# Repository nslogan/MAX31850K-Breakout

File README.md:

# MAX31850K-Breakout

## Description

A small breakout board for the Maxim MAX31850K 1-wire type-K thermocouple amplifier with CJC. Project [available on GitHub](https://github.com/nslogan/MAX31850K-Breakout").

## Production

The board measures 0.85x0.85in (21.62x21.62mm) and is designed for production at [OSH Park](https://www.oshpark.com/). The OSHPark DRU is located in the `res/` folder.

The boards can be purchased [here](https://oshpark.com/shared_projects/TtoEusV0) @ $3.60 for three.

## Parts

All parts on this board are from the [LoganSmith-Eagle-Library](https://github.com/nslogan/LoganSmith-Eagle-Library) available on GitHub (work in progress).

The BOM is located in the `release/` folder, all parts are sourced from Digi-Key.

## Project Structure

This project adheres to this structure:

	[ProjectName]
		README.md
		[release]
			[Major.Minor]
				ProjectName_BOM_Major.Minor.xls or ProjectName_BOM_BOM_Major.Minor.csv
				ProjectName_schematic_Major.Minor.pdf
				ProjectName_board-<top/mid#/bottom>_Major.Minor.png
				ProjectName_Major.Minor.sch
				ProjectName_Major.Minor.brd
				[Gerbers]
					...
			...
		[src]
			[Major.0]
				BoardName.sch
				BoardName.brd
				BOM.xls or BOM.csv
			[Major+1.0]
				...
			...
		[lib]
			...
		[res]
			Manufacturer.dru
			Manufacturer.cam

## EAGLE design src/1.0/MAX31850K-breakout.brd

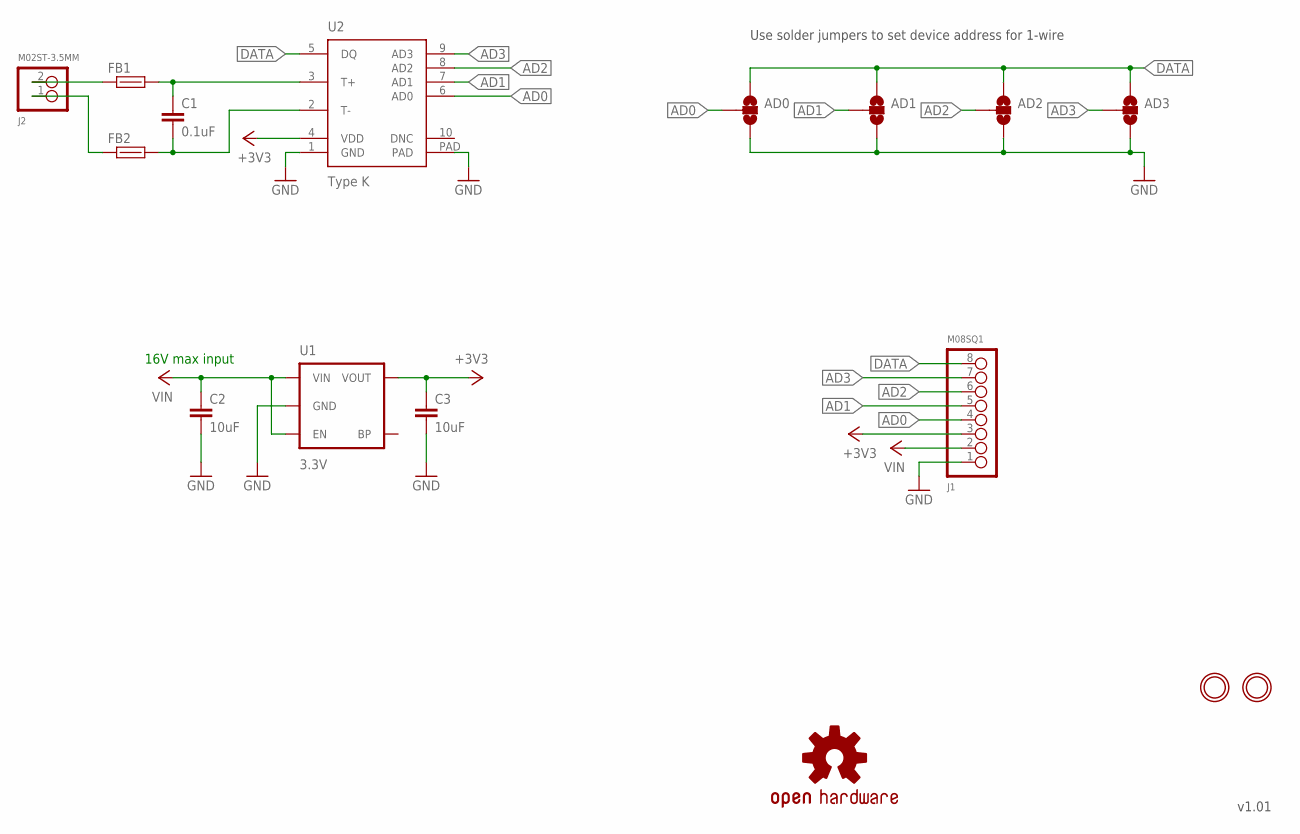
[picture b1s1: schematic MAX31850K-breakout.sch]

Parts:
AD0, AD1, AD2, AD3: SJ_2WAYS; SJ_3
C1: 0.1uF; 0603-CAP
C2: 10uF; 1206-CAP
C3: 10uF; 0805-CAP
FB1, FB2: FB-1K-100MHZ-0603; 0603-RES
J1: M08SQ1; 1X08_SQ1
J2: M02ST-3.5MM; SCREWTERMINAL-3.5MM-2
LOGO1: OSHW-LOGOM; OSHW-LOGO-M
U1: 3.3V; SOT23-5
U2: Type K; 10-TDFN-EP
U$1, U$2: MNTHOLE-2.0; MOUNTINGHOLE_2.0_PLATED

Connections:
+3V3: C3.P$1 (1), J1.3, U1.5 (VOUT), U2.4 (VDD)
AD0: AD0.2, J1.4, U2.6 (AD0)
AD1: AD1.2, J1.5, U2.7 (AD1)
AD2: AD2.2, J1.6, U2.8 (AD2)
AD3: AD3.2, J1.7, U2.9 (AD3)
DATA: AD0.1, AD1.1, AD2.1, AD3.1, J1.8, U2.5 (DQ)
GND: AD0.3, AD1.3, AD2.3, AD3.3, C2.P$4 (2), C3.P$2 (2), J1.1, U1.2 (GND), U2.1 (GND), U2.PAD
TM_FILT: C1.P$2 (2), FB2.P$2 (2), U2.2 (T-)
TM_RAW: FB2.P$1 (1), J2.1
TP_FILT: C1.P$1 (1), FB1.P$2 (2), U2.3 (T+)
TP_RAW: FB1.P$1 (1), J2.2
VIN: C2.P$3 (1), J1.2, U1.1 (VIN), U1.3 (EN)

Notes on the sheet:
16V max input
Use solder jumpers to set device address for 1-wire

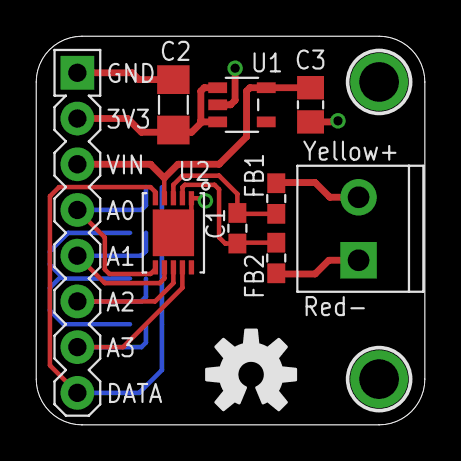
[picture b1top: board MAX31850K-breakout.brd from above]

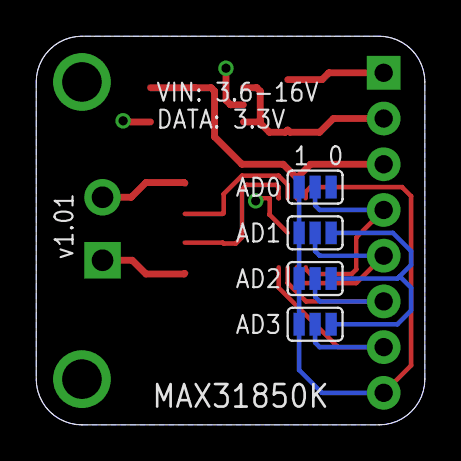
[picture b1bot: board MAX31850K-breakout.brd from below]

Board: 2 copper layers, 21.6 x 21.6 mm, 16 parts (4 on the bottom side), 12 nets.

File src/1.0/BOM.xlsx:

Part | Package | Description | DIGIKEY_OC | MFR | MPN | TEMP_RANGE | THICK | VALUE
C1 | 0603-CAP | 0.1uF CER CAP X7R +/-10% | 1276-1005-1-ND | Samsung Electro-Mechanics America, Inc | CL10B104KO8NNNC | -55C to 125C | 0.90mm | 0.1uF
C2 | 1206-CAP | 10uF CER CAP X7R +/-10% | 1276-3103-1-ND | Samsung Electro-Mechanics America, Inc | CL31B106KLHNNNE | -55C to 125C | 1.80mm | 10uF
C3 | 0805-CAP | 10uF CER CAP X7R +/-10% | 1276-1113-1-ND | Samsung Electro-Mechanics America, Inc | CL21B106KQQNNNE | -55C to 125C | 1.40mm | 10uF
FB1,FB2 | 0603-RES | 1k@100MHz ferrite bead | 1276-6378-1-ND | Samsung Electro-Mechanics America, Inc. | CIM10J102NC |  | 0.95mm | 1kOhm@100MHz
J1 | 1X08_SQ1 | 1x8 Headers Gold 30uin | 609-3273-ND | FCI | 68001-108HLF |  | 0.230in | 1x8
J2 | SCREWTERMINAL-3.5MM-2 | 2 pos 3.5mm screw terminal 7A 250V 18-26 AWG | A98036-ND | TE Connectivity | 1776275-2 | -55C to 105C |  | 7A 250V
U1 | SOT23-5 | Fixed output Texas Instruments LDO | 296-18476-1-ND | Texas Instruments | LP2985-33DBVR | -40C to 125C |  | 3.3V
U2 | 10-TDFN-EP | Cold-Junction Compensated, 1-Wire Thermocouple-to-Digital Converters | MAX31850KATB+-ND | Maxim Integrated | MAX31850KATB+ | -40C to 125C |  | Type K

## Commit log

2014-07-28 Added schematic and board.
2014-07-30 Almost have all components created in LoganSmith-Eagle-Library.
2014-08-01 Updated file structure to match PCBGuidelines structure (still in development). Preparing to move to release candidate.
2014-08-01 Slighly rearranged silk.
2014-08-01 Added BOM, still need part number for 1x8 header.
2014-08-02 Added 1x8 header to BOM.
2014-08-15 Create release folder, finalized BOM. Still need to make schematic PDF. Realized I need to make a hotfix 1.01 to correct board name - it's the MAX31850K, not the MAX31851K.
2014-08-15 Added PDF of schematic, pushing version 1.0.
2014-08-15 Fixed the MAX31851K to be MAX31850K on the bottom silk.
2014-08-15 Added 1.01 files.
2014-08-22 Forgot to up the version on the silk. Added version to schematic. Both use global attribute called CVERSION.

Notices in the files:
parts and their libraries:
SparkFun-Aesthetics: Licensing: Creative Commons ShareAlike 4.0 International - https://creativecommons.org/licenses/by-sa/4.0
